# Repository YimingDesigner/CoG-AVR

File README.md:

# CoG-AVR

## Overview

Too many wires and utilities are required to flash a microcontroller, which not meets the elegant and minimalism taste of AVR chip.

Here we designed a minimum development board to flash programs to 4 pin AVR microcontrollers, accompanied by a utility called USBtiny. One with `SOIC` package can also be flashed using IC sockets.

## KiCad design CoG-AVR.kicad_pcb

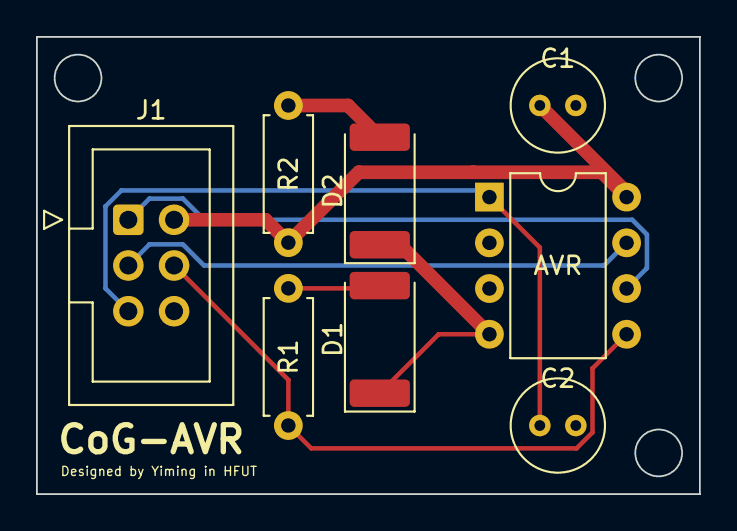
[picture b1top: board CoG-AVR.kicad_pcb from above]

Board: 2 copper layers, 36.8 x 25.4 mm, 8 parts (0 on the bottom side), 8 nets.

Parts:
AVR: ATtiny13A-P; DIP-8_W7.62mm
C1, C2: C; C_Radial_D5.0mm_H5.0mm_P2.00mm
D1: GREEN; LED_2512_6332Metric_Pad1.52x3.35mm_HandSolder
D2: RED; LED_2512_6332Metric_Pad1.52x3.35mm_HandSolder
J1: Conn_02x03; IDC-Header_2x03_P2.54mm_Vertical
R1, R2: R; R_Axial_DIN0207_L6.3mm_D2.5mm_P7.62mm_Horizontal

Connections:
+5V: AVR.8 (VCC), C1.1, J1.2, R2.2
/MISO: AVR.6 (PB1), J1.1
/MOSI: AVR.5 (PB0), J1.4, R1.2
/RST: AVR.1 (~RESET/PB5), C2.1, J1.5
/SCK: AVR.7 (PB2), J1.3
GND: AVR.4 (GND), C1.2, C2.2, D1.1 (K), D2.1 (K), J1.6
unnamed: D1.2 (A), R1.1
unnamed: D2.2 (A), R2.1

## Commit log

2022-11-23 refactor: rearrange folders
2022-11-23 docs: update documentation
2022-11-23 docs: revise spelling and grammar
